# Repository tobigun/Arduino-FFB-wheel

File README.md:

# Customized Arduino-FFB-wheel for Guillemot Force Feedback Racing Wheel
## About this project
### Motivation
It gets more and more difficult to find working Windows 11 drivers for this wheel.

Even the old [Vista drivers](https://support.thrustmaster.com/en/product/ffdrw-en/) which worked fine for me some years ago only work with the iRacing FFB test program (WheelCheck.exe) anymore, but not with any of my games - they simply crash. I already replaced "System32/immpid.dll" with the one from "SysWOW64" and although this fixes the crashes I do not get any Force Feedback effects in games at all (the green effect LED on the Main PCB also does not blink).

There is also another old [driver on archive.org](https://archive.org/details/Guillemot-Thrustmaster-ForceFeedback-wheel-64bit-driver) which is supposed to work according to some forums. But even after disabling the Windows driver signature check the driver was marked as non-functional in the device manager and was not functional.

As a consequence I decided to reverse engineer the hardware and replace the Main PCB of the wheel with an Arduino Pro Micro board. This way it supports Force Feedback via USB HID and does not need any drivers at all.
The nice thing about this wheel is that the Motor Control PCB can be reused and only the Logic Board has to be replaced.

For the firmware I tried multiple projects, e.g.:
- [ranenbg/Arduino-FFB-wheel](https://github.com/ranenbg/Arduino-FFB-wheel)
- [vsulako/AFFBWheel](https://github.com/vsulako/AFFBWheel) (see my [unfinished fork here](https://github.com/tobigun/AFFBWheel))
- [YukMingLaw/ArduinoJoystickWithFFBLibrary](https://github.com/YukMingLaw/ArduinoJoystickWithFFBLibrary)

Arduino-FFB-wheel was the most complete, so this project was used as the foundation.

### Game Compatibility Matrix
|Game|Store|Status|
|----|----|---|
|Assetto Corsa|Steam|OK
|Assetto Corsa Competizione|Steam|OK
|DiRT Rally 2.0|Steam|OK|
|Forza Horizon 4|Steam|OK. Requires the [Steering Wheel HID Profile](#hid-profiles), otherwise wheel will not be detected.|
|Forza Horizon 5|Steam|OK. Requires the [Generic HID Profile](#hid-profiles), otherwise game will crash at start.|
|NFS Heat|Steam|Only Steering, no FFB effects|
|NFS Hot Pursuit Remastered|Steam|OK|
|NFS Most Wanted|Steam|OK. Seems to support vibrations only, as FFB effects are week.|
|NFS Undercover|Steam|OK|

### Firmware
This repo is a fork of Miloš Ranković's [Arduino-FFB-wheel](https://github.com/ranenbg/Arduino-FFB-wheel), customized for the Guillemot Force Feedback Racing Wheel. As none of the pre-compiled binaries of the original project were suitable for this wheel, this project provides a configuration for the hardware and some minor software adjustments.

**Hardware configuration:**
- Analog X-Axis
- Hat Switch
- PWM motor control in 0-50-100 mode (hardcoded, so no need to configure it via the config software)
- Matrix keypad with 12 buttons
- Usage of 5 analog axis:
  - X-Axis (wheel angle)
  - Throttle
  - Brake
  - 2x analog levers on the wheel
- Force Feedback (of course)

### Original PCBs
The wheel consists of five PCBs:

- Main PCB, i.e. the logic board with the I-Force 2.0 chip:<br>

- Motor PCB (contains the PWM H-Bridge):<br>

- Front Button PCB:<br>

- Gear Shift PCB:<br>

- Power PCB (Note: already modified on the pictures). Contains power connector and switch, pedal connector and a digital switch (74HC4066). The 74HC4066 disables the two analog levers on the wheel when the pedals are connected.<br>

All PCBs connected:

### Arduino Main PCB
All of the original PCBs will be reused. The only PCB that will be replaced is the Main PCB. Instead an Arduino Pro Micro is used. I placed it on the Power PCB:

#### Wiring
Here is the overview of the connectors that are located on the Main PCB that now have to be connected to the Arduino board instead:

<table>
<tr><th colspan="3">Connector</th><th rowspan="2">Signal</th><th rowspan="2">Pin (ESP32-S3)</th><th rowspan="2">Pin (Pro Micro)</th><th rowspan="2">Comment</th></tr>
<tr><th>Name</th><th>Pin</th><th>Color</th></tr>

<tr><td rowspan="6">J5 (Motor PCB Connector)</td>
    <td>1</td><td style="background:green">green</td><td>Motor PWM</td><td>GP42</td><td>D9</td>
    <td rowspan="6">* Motor Enable switch must be connected to GP39/D10 via a BJT transistor to make sure that the motor is disabled when the microcontroller is powered down (i.e. not connected to USB).<br>
    This is necessary as the Motor PCB would erroneously interpret the missing PWM signal to apply maximum force. It would turn the wheel with full force in one direction and try to move it past the end stop. As this is not possible the motor gets quite hot after some minutes.
    <br>See schematic for more info.
    </td></tr>
<tr><td>2</td><td style="background:yellow">yellow</td><td>Motor Enable switch</td><td>[GP41]*</td><td>[D10]*</td></tr>
<tr><td>3</td><td style="background:orange">orange</td><td>GND</td><td colspan="2">GND</td></tr>
<tr><td>4</td><td style="background:red">red</td><td>GND</td><td colspan="2">GND</td></tr>
<tr><td>5</td><td style="background:brown">brown</td><td>GND</td><td colspan="2">GND</td></tr>
<tr><td>6</td><td style="background:black;color:white">black</td><td>+20V (from power supply)</td><td colspan="2">- (unused)</td></tr>

<tr><td rowspan="3">J6 (X-Axis Potentiometer)</td>
    <td>1</td><td style="background:orange">orange</td><td>VCC</td><td colspan="2">VCC</td><td rowspan="3"></td></tr>
<tr><td>2</td><td style="background:white">white</td><td>Analog X-Axis (0 .. VCC)</td><td>A0</td><td>A0</td></tr>
<tr><td>3</td><td style="background:green">green</td><td>GND</td><td colspan="2">GND</td></tr>

<tr><td rowspan="3">J7 (Y-Axis Potentiometer)</td>
    <td>1</td><td style="background:red">red</td><td>74HC4066 Supply Voltage</td><td colspan="2">VCC</td><td rowspan="3"></td></tr>
<tr><td>2</td><td style="background:blue;color:white">blue</td><td>Analog Y-Axis (0 .. VCC)</td><td>A1</td><td>A1</td></tr>
<tr><td>3</td><td style="background: repeating-linear-gradient(45deg,#eee,#eee 4px,#ccc 4px,#ccc 8px);">n.c.</td><td>-</td><td colspan="2">-</td></tr>

<tr><td rowspan="3">J8 (Z-Axis Potentiometer)</td>
    <td>1</td><td style="background:orange">orange</td><td>VCC</td><td colspan="2">VCC</td><td rowspan="3"></td></tr>
<tr><td>2</td><td style="background:brown">brown</td><td>Analog Z-Axis (0 .. VCC)</td><td>A3</td><td>A2</td></tr>
<tr><td>3</td><td style="background:green">green</td><td>GND</td><td colspan="2">GND</td></tr>

<tr><td rowspan="12">J12 (Button Matrix)</td>
    <td>1</td><td style="background:black;color:white">black</td><td>Matrix column 1</td><td>GP38</td><td>D5</td><td rowspan="12"></td></tr>
<tr><td>2</td><td style="background:brown">brown</td><td>Matrix column 2</td><td>GP37</td><td>D14</td></tr>
<tr><td>3</td><td style="background:red">red</td><td>Matrix column 3</td><td>GP36</td><td>D15</td></tr>
<tr><td>4</td><td style="background:orange">orange</td><td>Matrix column 4</td><td>GP35</td><td>D2</td></tr>
<tr><td>5</td><td style="background:yellow">yellow</td><td>Matrix row 1</td><td>GP17</td><td>D6</td></tr>
<tr><td>6</td><td style="background:green">green</td><td>Matrix row 2</td><td>GP33</td><td>D7</td></tr>
<tr><td>7</td><td style="background:blue;color:white">blue</td><td>Matrix row 3</td><td>GP18</td><td>D1 (TX0)</td></tr>
<tr><td>8</td><td style="background:#add8e6">light blue</td><td>Matrix row 4</td><td>GP34</td><td>D4</td></tr>
<tr><td>9</td><td style="background:#d3d3d3">light grey</td><td>Gear Shifter - Up (Matrix column 1)</td><td>GP38</td><td>D5</td></tr>
<tr><td>10</td><td style="background:grey">grey</td><td>Gear Shifter - Down (Matrix column 2)</td><td>GP37</td><td>D14</td></tr>
<tr><td>11</td><td style="background: repeating-linear-gradient(45deg,#eee,#eee 4px,#ccc 4px,#ccc 8px);">n.c.</td><td>-</td><td colspan="2">-</td></tr>
<tr><td>12</td><td style="background:white">white</td><td>Gear Shifter - Matrix row (Matrix row 2)</td><td>GP33</td><td>D7</td></tr>

<tr><td rowspan="4">J13 (Front LED)</td>
    <td>1</td><td style="background:#ff66cc">rose</td><td>LED Anode (+)</td><td>[GP40]*</td><td>[D3]*</td><td rowspan="4">* Connect LED's Anode via 820 Ohms resistor to pin.<br>See schematic for more info.</td></tr>
<tr><td>2</td><td style="background:black;color:white">black</td><td>LED Cathode (-)</td><td colspan="2">GND</td></tr>
<tr><td>3</td><td style="background: repeating-linear-gradient(45deg,#eee,#eee 4px,#ccc 4px,#ccc 8px);">n.c.</td><td>-</td><td colspan="2">-</td></tr>
<tr><td>4</td><td style="background: repeating-linear-gradient(45deg,#eee,#eee 4px,#ccc 4px,#ccc 8px);">n.c.</td><td>-</td><td colspan="2">-</td></tr>

<tr><td rowspan="4">JP101 (Analog Levers)<br>[Optional]</td>
    <td>1</td><td style="background:orange">orange</td><td>VCC</td><td colspan="2">VCC</td>
    <td rowspan="4">Wires can be unsoldered from connector JP101 of the power PCB and directly connected to the microcontroller.
    This way the pedals and levers can be used in parallel (5 instead of 3 axes). The Pins 2+3 on the JP101 connector on the power board should be pulled high then (i.e. connected to Pin 1).<br>See schematic for more info.</td></tr>
<tr><td>2</td><td style="background:red">red</td><td>Analog Axis - Lever left</td><td>A4</td><td>A3</td></tr>
<tr><td>3</td><td style="background:brown">brown</td><td>Analog Axis - Lever right</td><td>A5</td><td>A8</td></tr>
<tr><td>4</td><td style="background:green">green</td><td>GND</td><td colspan="2">GND</td></tr>

<tr><td rowspan="2">Blue Front LED<br>[Optional]</td>
    <td>A</td><td style="background:blue"></td><td>LED Anode (+)</td><td>[GP39]*</td><td>[D0]* (RX1)</td>
    <td rowspan="2">* Connect LED's Anode via 4.7 kOhms resistor to pin.<br>See schematic for more info.</td>
    </tr>
<tr><td>C</td><td style="background:black;color:white"></td><td>LED Cathode (-)</td><td colspan="2">GND</td></tr>

<tr><td rowspan="2">Green Front LED<br>[Optional]</td>
    <td>A</td><td style="background:green"></td><td>LED Anode (+)</td><td colspan="2">[+20V]*</td>
    <td rowspan="2">* Connect LED's Anode via 150 kOhms resistor to +20V.<br>See schematic for more info.</td>
    </tr>
<tr><td>C</td><td style="background:black;color:white"></td><td>LED Cathode (-)</td><td colspan="2">GND</td></tr>

<tr><td rowspan="2">Profile Switch<br>[Optional]</td>
    <td>1</td><td></td><td>Pin 1</td><td>GP7</td><td>D16</td>
    <td rowspan="2">For three pin switches: connect middle pin to D16 and any of the other two pins to GND.<br>
    </td></tr>
<tr><td>2</td><td style="background:black;color:white"></td><td>Pin 2</td><td colspan="2">GND</td></tr>
</table>

Make a little connector hub PCB to hold the motor switch transistor and  to connect all of the GND and VCC pins together. This way you can keep the existing connectors and you will still be able to reconnect them to the original Main PCB. But you can also cut the original connectors and solder the wires directly to the Arduino board.

#### HID Profiles
A Profile Switch can be added to select between to HID profiles:
- Switch open: Generic Joystick with generic X/Y/Z/Rx/Rz Axes (default)
- Switch closed: Steering wheel with Steering/Brake/Accelerator/Rx/Rz Axes

Switching profiles is necessary as there is no unified way to detect a Driving Wheel on Windows.
- Some games only detect a driving wheel if a Steering-Wheel Axis is present in the USB HID descriptor (e.g. Forza Horizon 4).
  - It seems that mostly older DirectInput based games require this profile as DirectInput uses a heuristic to detect wheels based on the axes of the controller ([see Wine DirectInput Port](https://github.com/wine-mirror/wine/blob/master/dlls/dinput/joystick_hid.c)).
- Some games require a generic X-Axis and do not work (or crash) when a Steering-Wheel Axis is present.
  - For example, Forza Horizons 5 crashes if a Steering-Wheel Axis is found.

##### Registry Tweak for Generic Profile
Instead of adding a switch to change the HID profile, for some games (like Forza Horizon 4) the Generic Profile also works if the following Windows registry keys are added via `regedit`:
```
Computer\HKEY_CURRENT_USER\System\CurrentControlSet\Control\MediaProperties\PrivateProperties\Joystick\OEM\VID_1B4F&PID_9206
Computer\HKEY_LOCAL_MACHINE\System\CurrentControlSet\Control\MediaProperties\PrivateProperties\Joystick\OEM\VID_1B4F&PID_9206
```
Add or modify the following value/data pair in these keys:
|Name|Type|Data
|----|----|----
|OEMData|REG_BINARY|43 00 88 01 fe 00 00 00

This can be achieved by double clicking on the `FFB_misc_programs/wheel-oemdata-add.reg` file.
The entries can be removed again with the `wheel-oemdata-remove.reg` file.

The bits of OEMData are described [here](https://sourceforge.net/p/timidity/git/ci/master/tree/windrv/mmddk.h#l230) but do not seem to be that important, as long as it starts with `43`.

See [Steam Community article on Forza Horizon 4 by LeadMagnet](https://steamcommunity.com/sharedfiles/filedetails/?id=2909923087) for more info.

> [!IMPORTANT]
> Make sure that the registry entries are removed again for Forza Horizons 5, as this game crahes if the entries are present.

------------------

# Arduino-FFB-wheel
A stand-alone DirectInput USB device is recognized in Windows as a joystick with force feedback functionality, based on BRWheel by Fernando Igor in 2017.

Firmware features:
- supported Arduino boards: Leonardo, Micro, and ProMicro (ATmega32U4, 5V, 16MHz)
- 4 analog axis + 1 for an optical or magnetic encoder, 2 FFB axis (with multichannel PWM or DAC output)
- for 2 FFB axis mode - 2 magnetic encoders may be used (for X and Y axis)
- automatic or manual analog axis calibration
- up to 16 buttons by 4x4 matrix or via **[button box firmware](https://github.com/ranenbg/Arduino-FFB-wheel/tree/master/tx_rw_ferrari_458_wheel_emu_16buttons)** uploaded to Arduino Nano/Uno
- up to 24 buttons by 3x8bit shift register chips
- analog XY H-pattern shifter (configurable to 6 or 8 gears + reverse gear, XY axis invert, reverse gear button invert)
- fully supported 16bit FFB effects (custom force effect not implemented)
- envelope and conditional block effects, start delay, duration, deadband, and direction enable
- FFB calculation and axis/button update rate 500Hz (2ms period)
- many firmware options (external 12bit ADC/DAC, automatic/manual pedal calibration, z-index support/offset/reset, hat switch, button matrix, external shift register, hardware wheel re-center, xy analog H shifter, FFB on analog axis)
- RS232 serial interface for configuring many firmware settings (10ms period)
- fully adjustable FFB output in the form of 4-channel digital 16bit PWM or 2-channel analog 12bit DAC signals
- available PWM modes: PWM+-, PWM+dir, PWM0-50-100, RCM (if 2 FFB axis: 2CH PWM+-, 2CH PWM+dir, 2CH PWM0-50-100, 2CH RCM)
- available DAC modes: DAC+-, DAC+dir, DAC0-50-100 (if 2 FFB axis: 1CH DAC+-, 2CH DAC+dir, 2CH DAC0-50-100)
- load cell support for 24bit HX711 chip (for Y axis only)
- all firmware settings are stored in EEPROM (and automatically loaded at each Arduino powerup)
- original wheel control user interface **[Arduino FFB gui](https://github.com/ranenbg/Arduino-FFB-gui)** for an easy configuration and monitoring of all inputs/outputs 

Detailed documentation and more information about the firmware can be found in txt files inside the `docs/fw` folder.

# Firmware pinouts and wiring diagrams

**Note:** some pin mappings in the image are outdated. Check the wiring table above for the correct ones.
## Optical encoder and LED wiring

## Button matrix pinouts

**Note:** the digital inputs for the matrix are not correct in the image. Check the wiring table above for the correct ones.

## Firmware upload procedure
You can use XLoader from the `misc_programs/XLoader` folder:
- set 57600baud, ATmega32U4 microcontroller and select desired HEX
- press the reset button on Arduino (or shortly connect the RST pin to GND)
- select the newly appeared COM port (Arduino in bootloader mode*) and press upload, you will only have a few seconds

*It is possible that some cheap Chinese clones of Arduino Leonardo, Micro, or ProMicro do not have a bootloader programmed. In that case you need to upload the original Arduino Leonardo bootloader first. You can find more details about it here: https://docs.arduino.cc/built-in-examples/arduino-isp/ArduinoISP

## How to compile the source
In order to compile the firmware yourself you may use Windows 11, you need to install Arduino IDE v2.3.6 and Arduino Boards v1.8.7. You must place the libraries (from the `libraries` folder) in your `.../documents/Arduino/Libraries` folder.

## Credits
- Miloš Ranković: [Arduino-FFB-wheel](https://github.com/ranenbg/Arduino-FFB-wheel)
- FFB HID and USB core for Arduino by: Peter Barrett
- BRWheel firmware by: Tero Loimuneva, Saku Kekkonen, Etienne Saint-Paul, and Fernando Igor
https://github.com/fernandoigor/BRWheel/tree/alphatest

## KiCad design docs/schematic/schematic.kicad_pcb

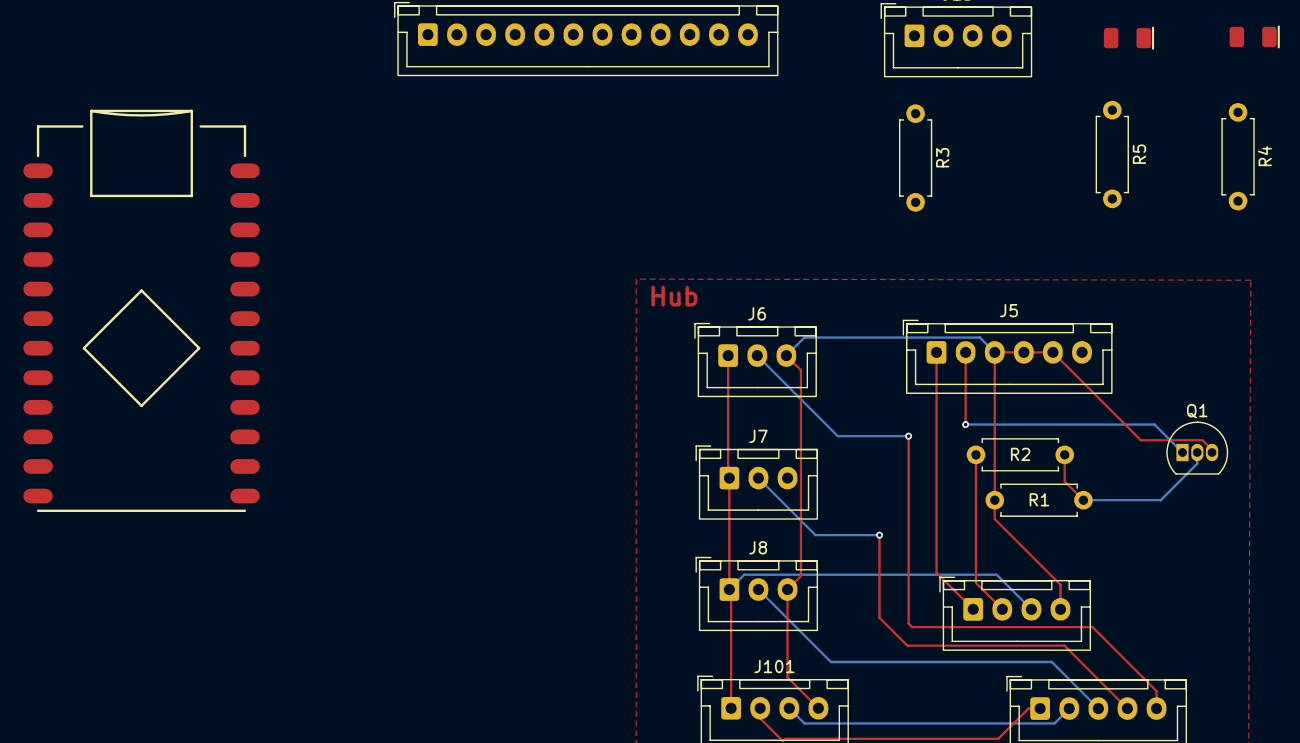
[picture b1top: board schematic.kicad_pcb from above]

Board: 2 copper layers, 18 parts (0 on the bottom side), 25 nets.

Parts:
D2: Green; LED_1206_3216Metric_Red
D3: Blue; LED_1206_3216Metric_Blue
J1, J101: Analog Levers; JST_XH_B4B-XH-A_1x04_P2.50mm_Vertical
J2: JST_XH_B5B-XH-A_1x05_P2.50mm_Vertical
J5: Motor-PCB; JST_XH_B6B-XH-A_1x06_P2.50mm_Vertical
J6: X-Axis; JST_XH_B3B-XH-A_1x03_P2.50mm_Vertical
J7: Y-Axis; JST_XH_B3B-XH-A_1x03_P2.50mm_Vertical
J8: Z-Axis; JST_XH_B3B-XH-A_1x03_P2.50mm_Vertical
J12: Button Matrix; JST_XH_B12B-XH-A_1x12_P2.50mm_Vertical
J13: Front LED; JST_XH_B4B-XH-A_1x04_P2.50mm_Vertical
Q1: BC548; TO-92_Inline
R1, R4: 4.7k; R_Axial_DIN0207_L6.3mm_D2.5mm_P7.62mm_Horizontal
R2: 10k; R_Axial_DIN0207_L6.3mm_D2.5mm_P7.62mm_Horizontal
R3: 820; R_Axial_DIN0207_L6.3mm_D2.5mm_P7.62mm_Horizontal
R5: 150k; R_Axial_DIN0207_L6.3mm_D2.5mm_P7.62mm_Horizontal
U1: ProMicroC

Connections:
20V: J5.6, R5.2
/Motor_Enable: J5.2, Q1.1 (C)
/Motor_PWM: J1.1, J5.1, U1.12 (D9/A9)
GND: D2.1 (K), D3.1 (K), J1.4, J5.3, J5.4, J5.5, J6.3, J8.3, J13.2, J101.4, Q1.3 (E), R1.2, U1.3 (GND), U1.4 (GND), U1.23 (GND)
Matrix_Col1: J12.1, J12.9, U1.8 (D5)
Matrix_Col2: J12.2, J12.10, U1.15 (D14)
Matrix_Col3: J12.3, U1.16 (D15)
Matrix_Col4: J12.4, U1.5 (D2)
Matrix_Row1: J12.5, U1.9 (D6/A7)
Matrix_Row2: J12.6, J12.12, U1.10 (D7)
Matrix_Row3: J12.7, U1.11 (D8/A8)
Matrix_Row4: J12.8, U1.7 (D4/A6)
unnamed: D2.2 (A), R5.1
unnamed: D3.2 (A), R4.1
unnamed: J2.5, J6.2, U1.17 (A0)
unnamed: J2.4, J7.2, U1.18 (A1)
unnamed: J2.3, J8.2, U1.19 (A2)
unnamed: J13.1, R3.1
unnamed: J2.1, J101.2, U1.20 (A3)
unnamed: J2.2, J101.3, U1.13 (D10/A10)
unnamed: Q1.2 (B), R1.1, R2.2
unnamed: R3.2, U1.6 (D3)
unnamed: J1.2, R2.1, U1.14 (D16)
unnamed: R4.2, U1.2 (RX)
VCC: J1.3, J6.1, J7.1, J8.1, J101.1, U1.21 (5V)

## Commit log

2026-01-04 config and modify for Guillemot wheel
2026-01-07 update data LED
2026-01-07 add motor switch ltspice simulation
2026-01-07 remove obsolete pre-compiled firmware files
2026-01-07 remove simulator
2026-01-07 adjust USB descriptors
2026-01-07 fix motor enable switch
2026-01-07 move documentation
2026-01-08 add documentation
2026-01-20 move simulation
2026-01-20 fix JP101 pin order
2026-01-20 add schematic
2026-01-20 switch brake and accelerator axes
2026-01-24 update gitignore
2026-01-24 hardcode pwm mode
2026-01-24 update motor schema
2026-01-24 update wiring
2026-01-24 fix AVG_INPUTS
2026-01-24 simplify code
2026-01-24 simplify config
2026-01-24 average axes
2026-01-25 de-jitter x-axis
2026-01-25 make CDC deactivatable
2026-01-25 update schematic
2026-01-25 add RAM pool MEMORY_SIZE
2026-01-25 add missing include
2026-01-25 update to AVR Arduino 1.8.7 framework
2026-01-25 mark USBCore changes
2026-01-31 convert to platformio project
2026-01-31 rename ino to cpp
2026-01-31 fix compile errors
2026-01-31 remove unused files
2026-01-31 change default config to 0..50.100 mode and 20kHz
2026-01-31 detect pedal removal
2026-02-01 support two profiles
2026-02-01 fix force feedback for steering wheel profile
2026-02-01 document changes
2026-02-02 fix Forza Horizon 5
2026-02-02 add profile switch
2026-02-02 remove physical hid descriptors
2026-02-02 indent HID report
2026-02-02 add regions to HID descriptor
2026-02-02 remove unused features and clean up
2026-02-03 cleanup code
2026-02-03 more clean-up
2026-02-03 remove usage of CPR
2026-02-03 tweak UI
2026-02-03 fix offsets for steering mode
2026-02-04 replace running average with normal average for better feedback
2026-02-04 reset ROTATION_DEG to 1080° for stronger force feedback effects
2026-02-04 fix pedal detection
2026-02-04 cleanup
2026-02-04 more cleanup
2026-02-04 separate ffb and hid precision definitions
2026-02-05 add x-axis scaling
2026-02-06 set usb product name via platform.ini
2026-02-07 support for combined axis
2026-02-07 add force diagram
2026-02-09 support for esp32
2026-02-12 enable tinyusb
2026-02-12 remove extensions.json
2026-02-12 remove vscode folder
2026-02-15 add pwm support for ESP32
2026-02-15 rename to main
2026-02-15 fix report sizes
2026-02-15 fix pwm
2026-02-15 use real axis data
2026-02-16 cleanup input pins
2026-02-17 fix axis and profile switch
2026-02-17 rename to lowercase
2026-02-17 lowercase
2026-02-17 remove var for profile id
2026-02-17 move all doc into one folder
2026-02-17 move all programs into one folder
2026-02-17 use lowercase files
2026-02-17 use lowercase
2026-02-17 rename source folder
2026-02-17 fix buttons
2026-02-17 set usb device name
2026-02-18 fix input matrix init
2026-02-21 improve latency for ESP32
2026-02-21 fix pro micro
2026-02-21 fix FFB Clip LED
2026-02-21 adjust sampleing requency
2026-02-21 check for race conditions
2026-02-21 combine vsulako and ranenbg implementations
2026-02-21 add profile for wheel control program
